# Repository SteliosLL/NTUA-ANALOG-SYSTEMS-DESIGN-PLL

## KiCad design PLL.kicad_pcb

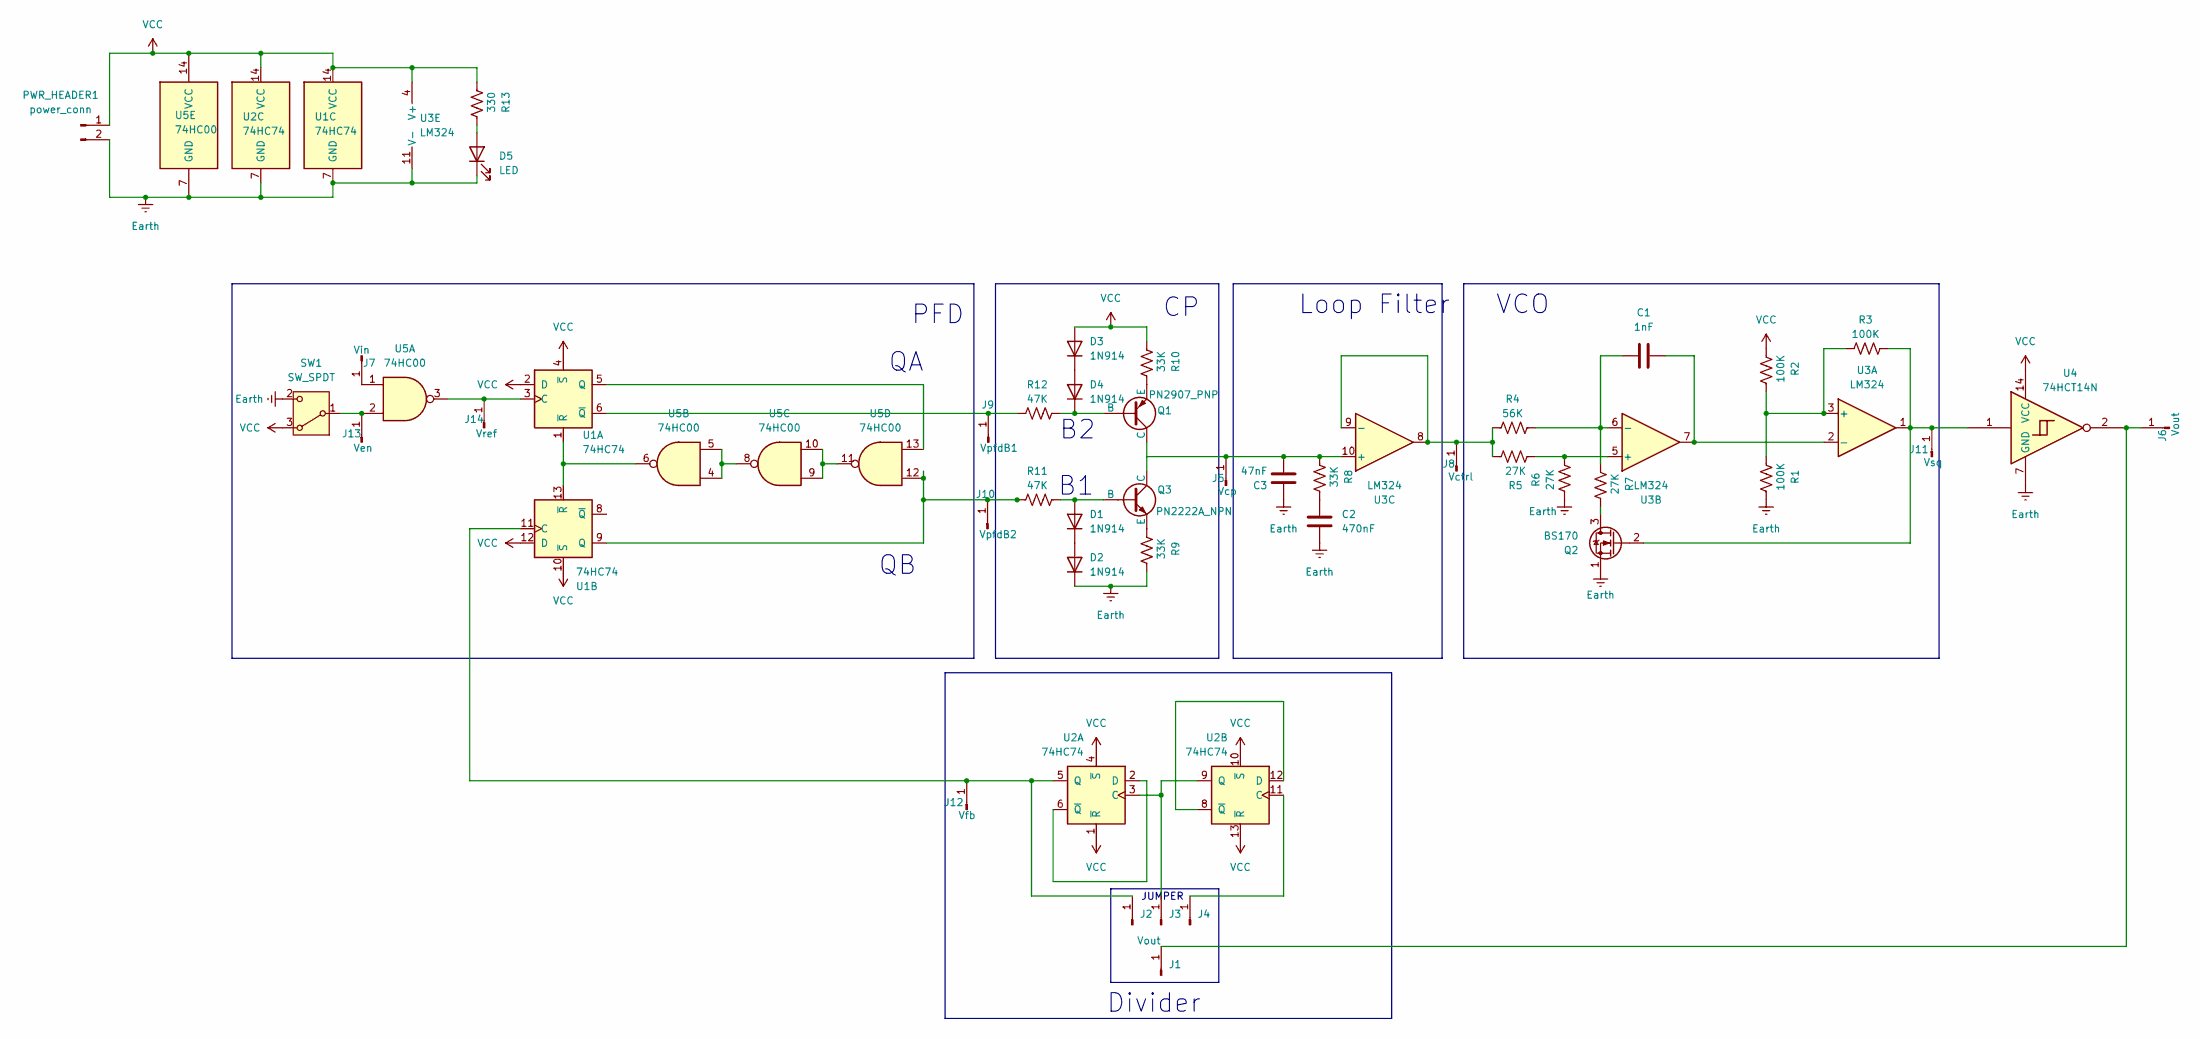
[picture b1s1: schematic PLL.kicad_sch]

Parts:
C1: 1nF; C_Disc_D7.5mm_W2.5mm_P5.00mm
C2: 470nF; C_Disc_D7.5mm_W2.5mm_P5.00mm
C3: 47nF; C_Disc_D7.5mm_W2.5mm_P5.00mm
D1, D2, D3, D4: 1N914; D_DO-35_SOD27_P7.62mm_Horizontal
D5: LED; LED_D5.0mm
J1, J6: Vout; PinHeader_1x01_P2.54mm_Vertical
J2: M=1; PinHeader_1x01_P2.54mm_Vertical
J3: M=2; PinHeader_1x01_P2.54mm_Vertical
J4: M=4; PinHeader_1x01_P2.54mm_Vertical
J5: Vcp; PinHeader_1x01_P2.54mm_Vertical
J7: Vin; PinHeader_1x01_P2.54mm_Vertical
J8: Vctrl; PinHeader_1x01_P2.54mm_Vertical
J9: VpfdB1; PinHeader_1x01_P2.54mm_Vertical
J10: VpfdB2; PinHeader_1x01_P2.54mm_Vertical
J11: Vsq; PinHeader_1x01_P2.54mm_Vertical
J12: Vfb; PinHeader_1x01_P2.54mm_Vertical
J13: Ven; PinHeader_1x01_P2.54mm_Vertical
J14: Vref; PinHeader_1x01_P2.54mm_Vertical
PWR_HEADER1: power_conn; PinHeader_1x02_P2.54mm_Vertical
Q1: PN2907_PNP; TO-92_Inline
Q2: BS170; TO-92_Inline
Q3: PN2222A_NPN; TO-92_Inline
R1, R2, R3: 100K; R_Axial_DIN0204_L3.6mm_D1.6mm_P7.62mm_Horizontal
R4: 56K; R_Axial_DIN0204_L3.6mm_D1.6mm_P7.62mm_Horizontal
R5, R6, R7: 27K; R_Axial_DIN0204_L3.6mm_D1.6mm_P7.62mm_Horizontal
R8, R9, R10: 33K; R_Axial_DIN0204_L3.6mm_D1.6mm_P7.62mm_Horizontal
R11, R12: 47K; R_Axial_DIN0204_L3.6mm_D1.6mm_P7.62mm_Horizontal
R13: 330; R_Axial_DIN0204_L3.6mm_D1.6mm_P7.62mm_Horizontal
SW1: SW_SPDT; SW_Slide-03_Wuerth-WS-SLTV_10x2.5x6.4_P2.54mm
U1, U2: 74HC74; DIP-14_W7.62mm_Socket
U3: LM324; DIP-14_W7.62mm_Socket
U4: 74HCT14N; DIP-14_W7.62mm_Socket
U5: 74HC00; DIP-14_W7.62mm_Socket

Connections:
Earth: C2.2, C3.1, D2.1 (K), D5.1 (K), PWR_HEADER1.2, Q2.1 (S), R1.2, R6.1, R9.2, SW1.2 (C), U1.7 (GND), U2.7 (GND), U3.11 (V-), U4.7 (GND), U5.7 (GND)
unnamed: C2.1, R8.2
unnamed: D1.2 (A), Q3.2 (B), R11.2
unnamed: D1.1 (K), D2.2 (A)
unnamed: D3.1 (K), D4.2 (A)
unnamed: D4.1 (K), Q1.2 (B), R12.2
unnamed: D5.2 (A), R13.2
unnamed: J1.1, J6.1, U4.2
unnamed: J3.1, U2.3 (C), U2.9 (Q)
unnamed: J4.1, U2.11 (C)
unnamed: C3.2, J5.1, R8.1, U3.10 (+)
unnamed: J7.1, U5.1
unnamed: J8.1, R4.1, R5.2, U3.8, U3.9 (-)
unnamed: J9.1, R12.1, U1.6 (~Q)
unnamed: J10.1, R11.1, U1.9 (Q), U5.12
unnamed: J11.1, Q2.2 (G), R3.2, U3.1, U4.1
unnamed: J2.1, J12.1, U1.11 (C), U2.5 (Q)
unnamed: J13.1, SW1.1 (B), U5.2
unnamed: J14.1, U1.3 (C), U5.3
unnamed: Q1.3 (C), Q3.3 (C)
unnamed: Q1.1 (E), R10.2
unnamed: Q2.3 (D), R7.2
unnamed: Q3.1 (E), R9.1
unnamed: U1.5 (Q), U5.13
unnamed: U1.1 (~R), U1.13 (~R), U5.6
unnamed: U2.2 (D), U2.6 (~Q)
unnamed: U2.8 (~Q), U2.12 (D)
unnamed: R1.1, R2.2, R3.1, U3.3 (+)
unnamed: C1.2, U3.2 (-), U3.7
unnamed: R5.1, R6.2, U3.5 (+)
unnamed: C1.1, R4.2, R7.1, U3.6 (-)
unnamed: U5.4, U5.5, U5.8
unnamed: U5.9, U5.10, U5.11
VCC: D3.2 (A), PWR_HEADER1.1, R2.1, R10.1, R13.1, SW1.3 (A), U1.2 (D), U1.4 (~S), U1.10 (~S), U1.12 (D), U1.14 (VCC), U2.1 (~R), U2.4 (~S), U2.10 (~S), U2.13 (~R), U2.14 (VCC), U3.4 (V+), U4.14 (VCC), U5.14 (VCC)

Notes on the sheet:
Loop Filter
JUMPER
VCO
Divider
PFD

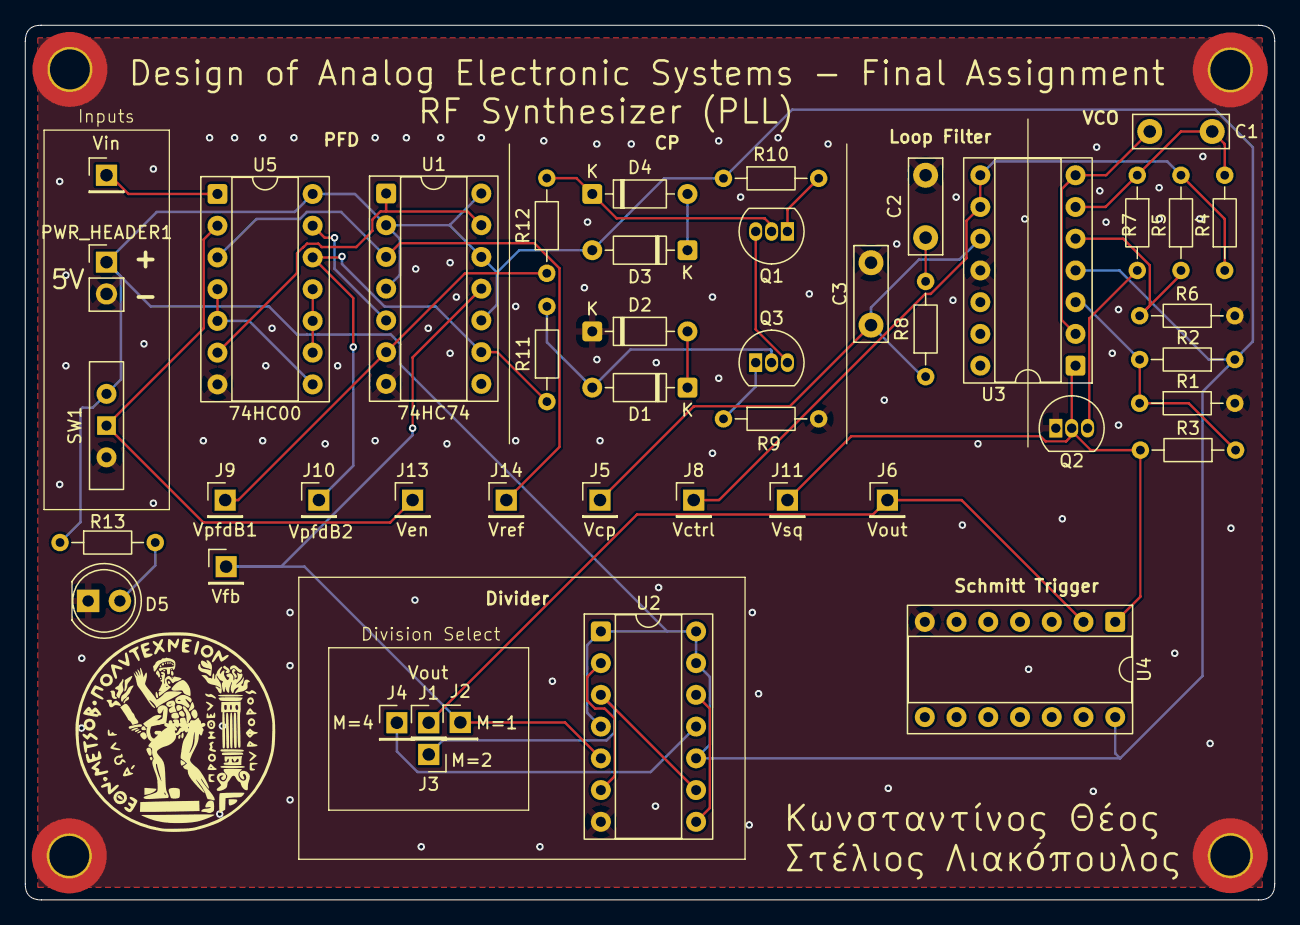
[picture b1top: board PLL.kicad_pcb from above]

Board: 2 copper layers, 100.0 x 70.0 mm, 45 parts (0 on the bottom side), 34 nets.

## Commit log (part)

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2026-05-17 create repo
2026-05-18 PCB design start
2026-05-21 FINISH
2026-05-21 add LED indicator
2026-06-17 Vsq connection fix
